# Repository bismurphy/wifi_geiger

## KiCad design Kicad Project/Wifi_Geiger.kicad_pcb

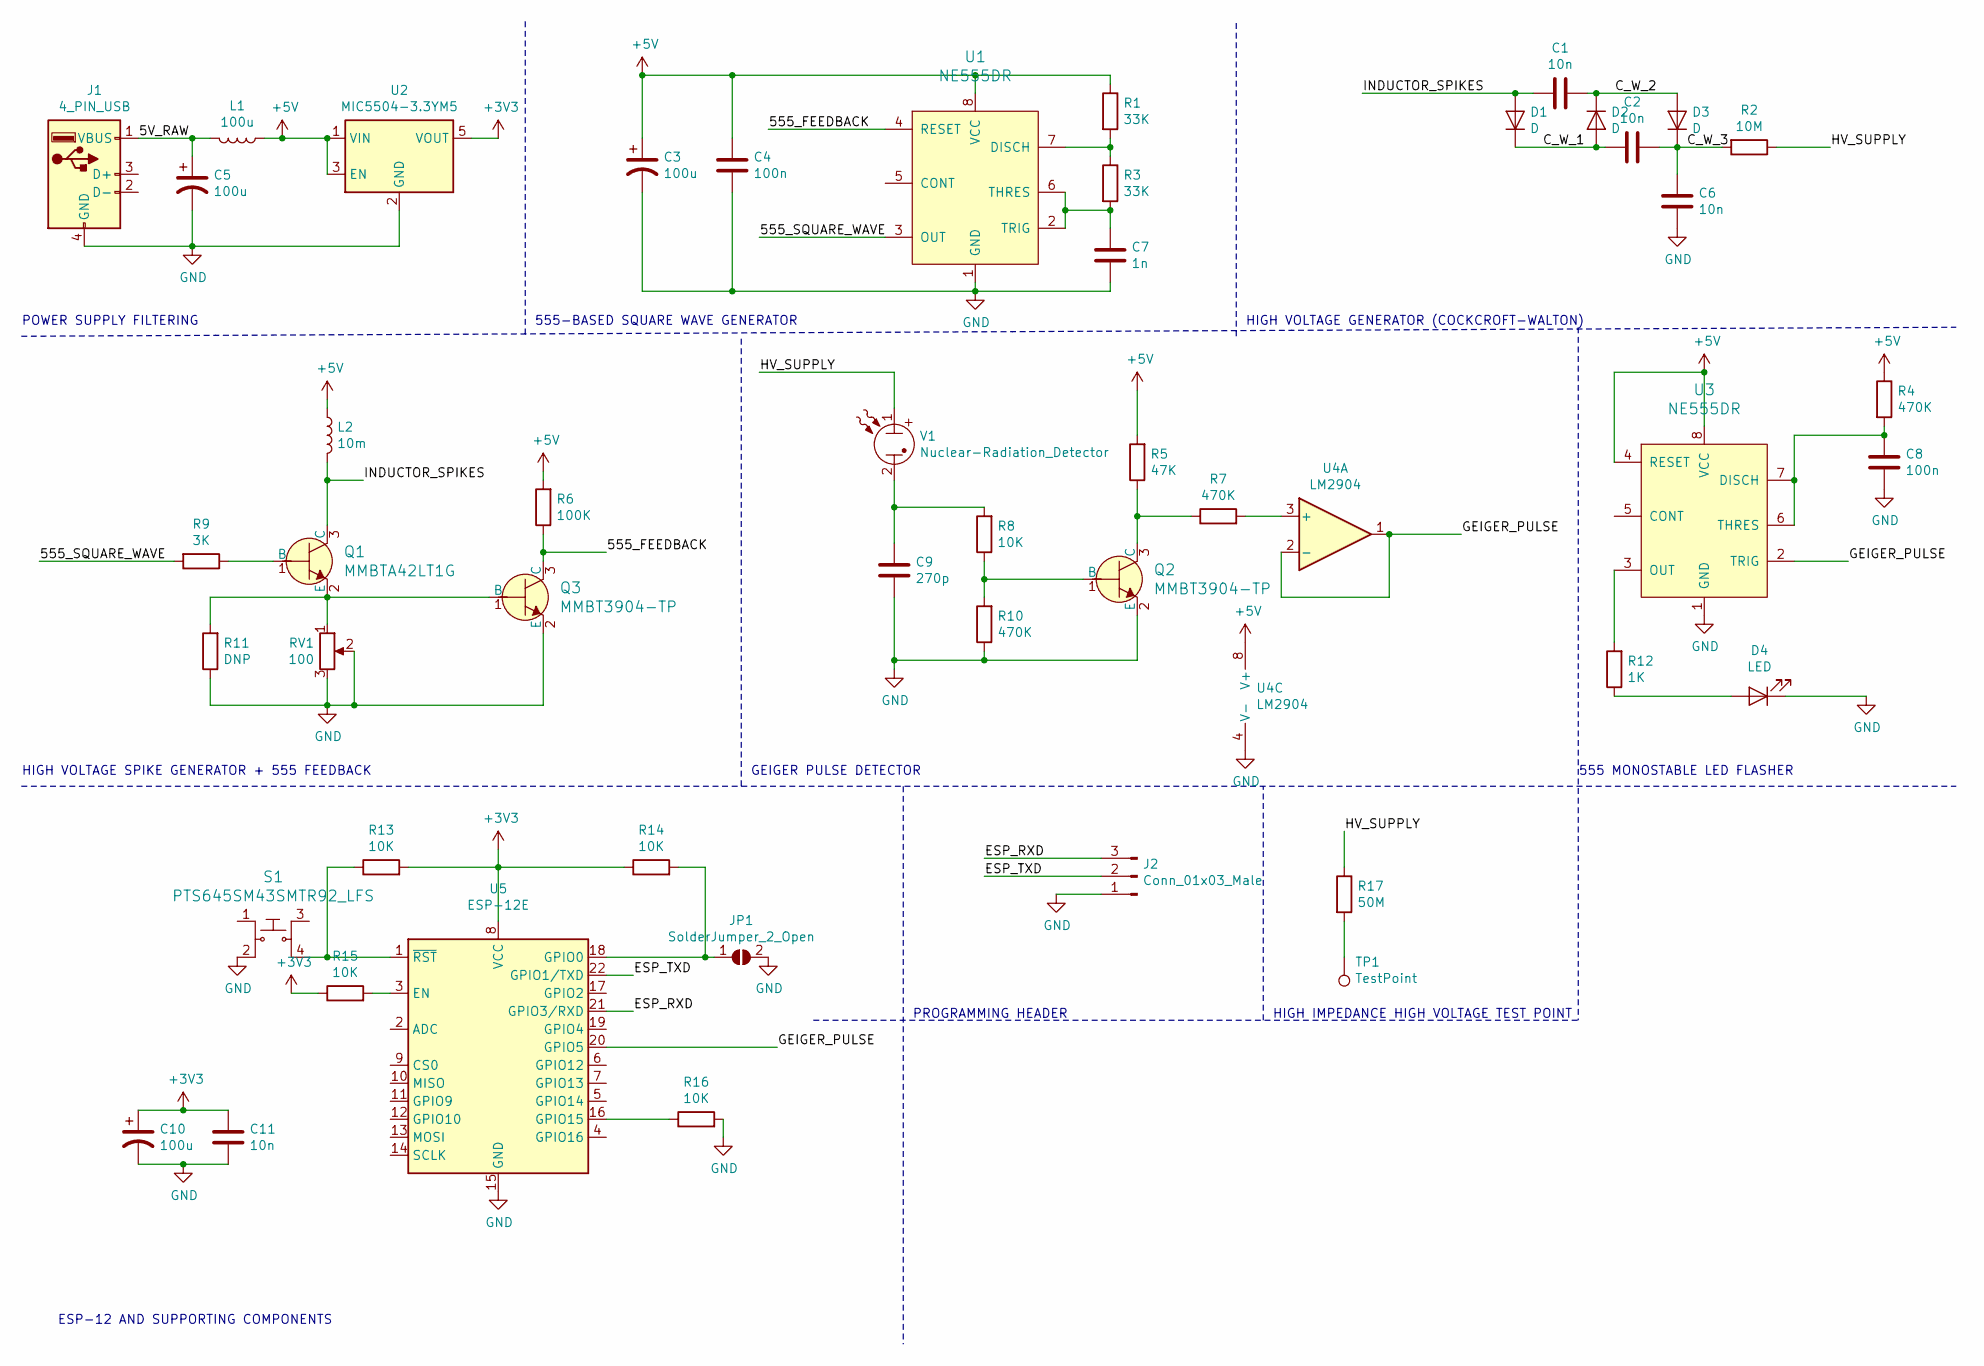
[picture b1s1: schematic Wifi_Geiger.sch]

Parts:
C1, C2, C6, C11: 10n; C_1206_3216Metric_Pad1.42x1.75mm_HandSolder
C3, C5, C10: 100u; CP_Elec_6.3x5.3
C4, C8: 100n; C_0603_1608Metric_Pad1.05x0.95mm_HandSolder
C7: 1n; C_0603_1608Metric_Pad1.05x0.95mm_HandSolder
C9: 270p; C_0603_1608Metric_Pad1.05x0.95mm_HandSolder
D1, D2, D3: D; D_SOD-123F
D4: LED; D_0603_1608Metric_Castellated
J1: 4_PIN_USB; usb-traces
J2: Conn_01x03_Male; PinHeader_1x03_P2.54mm_Vertical
JP1: SolderJumper_2_Open; SolderJumper-2_P1.3mm_Open_RoundedPad1.0x1.5mm
L1: 100u; L_0805_2012Metric_Pad1.15x1.40mm_HandSolder
L2: 10m; L_Bourns_SRR1210A
Q1: MMBTA42LT1G; SOT-23-3; MPN MMBTA42LT1G; Digi-Key_PN MMBTA42LT1GOSCT-ND
Q2, Q3: MMBT3904-TP; SOT-23-3; MPN MMBT3904-TP; Digi-Key_PN MMBT3904TPMSCT-ND
R1, R3: 33K; R_0603_1608Metric_Pad1.05x0.95mm_HandSolder
R2: 10M; R_0603_1608Metric_Pad1.05x0.95mm_HandSolder
R4, R7, R10: 470K; R_0603_1608Metric_Pad1.05x0.95mm_HandSolder
R5: 47K; R_0603_1608Metric_Pad1.05x0.95mm_HandSolder
R6: 100K; R_0603_1608Metric_Pad1.05x0.95mm_HandSolder
R8, R13, R14, R15, R16: 10K; R_0603_1608Metric_Pad1.05x0.95mm_HandSolder
R9: 3K; R_0603_1608Metric_Pad1.05x0.95mm_HandSolder
R11: DNP; R_0603_1608Metric_Pad1.05x0.95mm_HandSolder
R12: 1K; R_0603_1608Metric_Pad1.05x0.95mm_HandSolder
R17: 50M; R_0603_1608Metric_Pad1.05x0.95mm_HandSolder
RV1: 100; Potentiometer_Bourns_TC33X_Vertical
S1: PTS645SM43SMTR92_LFS; Switch_Tactile_SMD_6x6mm_PTS645; MPN PTS645SM43SMTR92 LFS; Digi-Key_PN CKN9112CT-ND
TP1: TestPoint; TestPoint_Pad_D2.5mm
U1, U3: NE555DR; SOIC-8_W3.9mm; MPN NE555DR; Digi-Key_PN 296-6501-1-ND
U2: MIC5504-3.3YM5; SOT-23-5
U4: LM2904; SOIC-8_3.9x4.9mm_P1.27mm
U5: ESP-12E
V1: Nuclear-Radiation_Detector; j305_geiger_fuse_holder

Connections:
+3V3: C10.1, C11.2, R13.2, R14.1, R15.1, U2.5 (VOUT), U5.8 (VCC)
+5V: C3.1, C4.1, L1.1, L2.1, R1.1, R4.1, R5.2, R6.2, U1.8 (VCC), U2.1 (VIN), U2.3 (EN), U3.4 (RESET), U3.8 (VCC), U4.8 (V+)
/5V_RAW: C5.1, J1.1 (VBUS), L1.2
/555_FEEDBACK: Q3.3 (C), R6.1, U1.4 (RESET)
/555_SQUARE_WAVE: R9.2, U1.3 (OUT)
/C_W_1: C2.2, D1.1 (K), D2.2 (A)
/C_W_2: C1.1, D2.1 (K), D3.2 (A)
/C_W_3: C2.1, C6.2, D3.1 (K), R2.2
/ESP_RXD: J2.3, U5.21 (GPIO3/RXD)
/ESP_TXD: J2.2, U5.22 (GPIO1/TXD)
/GEIGER_PULSE: U3.2 (TRIG), U4.1, U4.2 (-), U5.20 (GPIO5)
/HV_SUPPLY: R2.1, R17.1, V1.1
/INDUCTOR_SPIKES: C1.2, D1.2 (A), L2.2, Q1.3 (C)
GND: C3.2, C4.2, C5.2, C6.1, C7.2, C8.2, C9.1, C10.2, C11.1, D4.1 (K), J1.4 (GND), J2.1, JP1.2 (B), Q2.2 (E), Q3.2 (E), R10.1, R11.1, R16.2, RV1.2, RV1.3, S1.2, U1.1 (GND), U2.2 (GND), U3.1 (GND), U4.4 (V-), U5.15 (GND)
unnamed: C7.1, R3.2, U1.2 (TRIG), U1.6 (THRES)
unnamed: C8.1, R4.2, U3.6 (THRES), U3.7 (DISCH)
unnamed: C9.2, R8.2, V1.2
unnamed: D4.2 (A), R12.1
unnamed: JP1.1 (A), R14.2, U5.18 (GPIO0)
unnamed: Q1.1 (B), R9.1
unnamed: Q1.2 (E), Q3.1 (B), R11.2, RV1.1
unnamed: Q2.1 (B), R8.1, R10.2
unnamed: Q2.3 (C), R5.1, R7.1
unnamed: R1.2, R3.1, U1.7 (DISCH)
unnamed: R7.2, U4.3 (+)
unnamed: R12.2, U3.3 (OUT)
unnamed: R13.1, S1.4, U5.1 (~RST)
unnamed: R15.2, U5.3 (EN)
unnamed: R16.1, U5.16 (GPIO15)
unnamed: R17.2, TP1.1

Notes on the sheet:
POWER SUPPLY FILTERING
555-BASED SQUARE WAVE GENERATOR
HIGH VOLTAGE SPIKE GENERATOR + 555 FEEDBACK
HIGH VOLTAGE GENERATOR (COCKCROFT-WALTON)
GEIGER PULSE DETECTOR
555 MONOSTABLE LED FLASHER
ESP-12 AND SUPPORTING COMPONENTS
PROGRAMMING HEADER
HIGH IMPEDANCE HIGH VOLTAGE TEST POINT

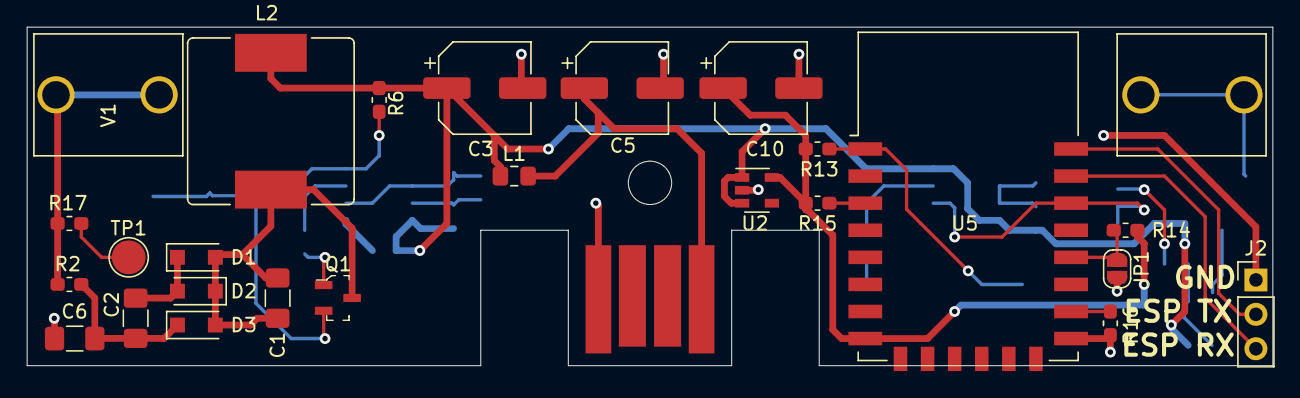
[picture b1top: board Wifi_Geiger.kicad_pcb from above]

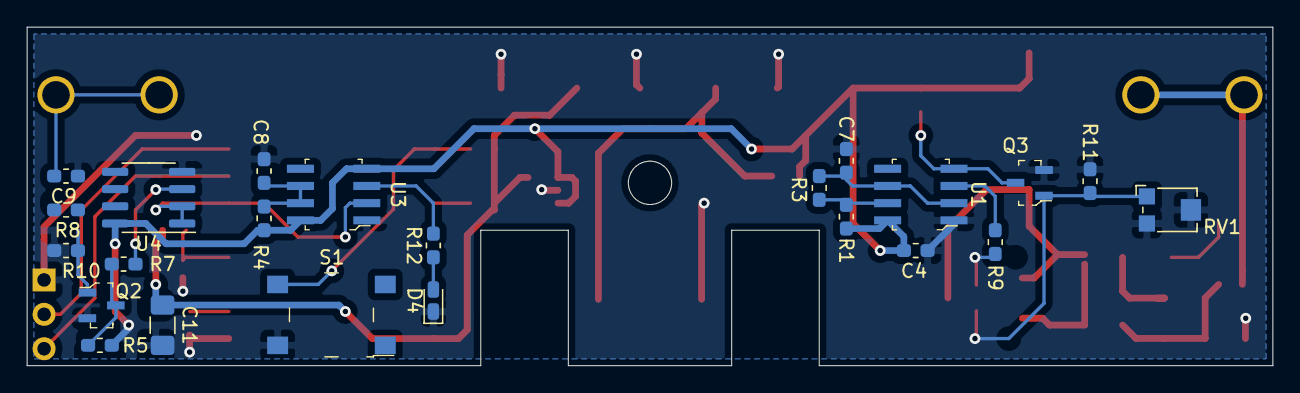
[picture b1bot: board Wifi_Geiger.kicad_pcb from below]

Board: 2 copper layers, 92.0 x 25.0 mm, 49 parts (23 on the bottom side), 30 nets.

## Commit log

2020-09-28 Added software in the state it was in on the initial prototype
2020-09-28 Arduino IDE needed slight folder reconfig
2020-11-04 Final commit for video
